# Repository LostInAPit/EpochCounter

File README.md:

# EpochCounter
A counter to count the days since a specific date using an Arduino nano, DS3231 RTC and a 4-digit 7 Segment display

I designed this project to be a simple, self contained display for your workspace, office or anywhere with access to wall power. The main use of the project is to count the days since a specific event, lifestyle change such as sobriety, mental health goals or really any other reason.

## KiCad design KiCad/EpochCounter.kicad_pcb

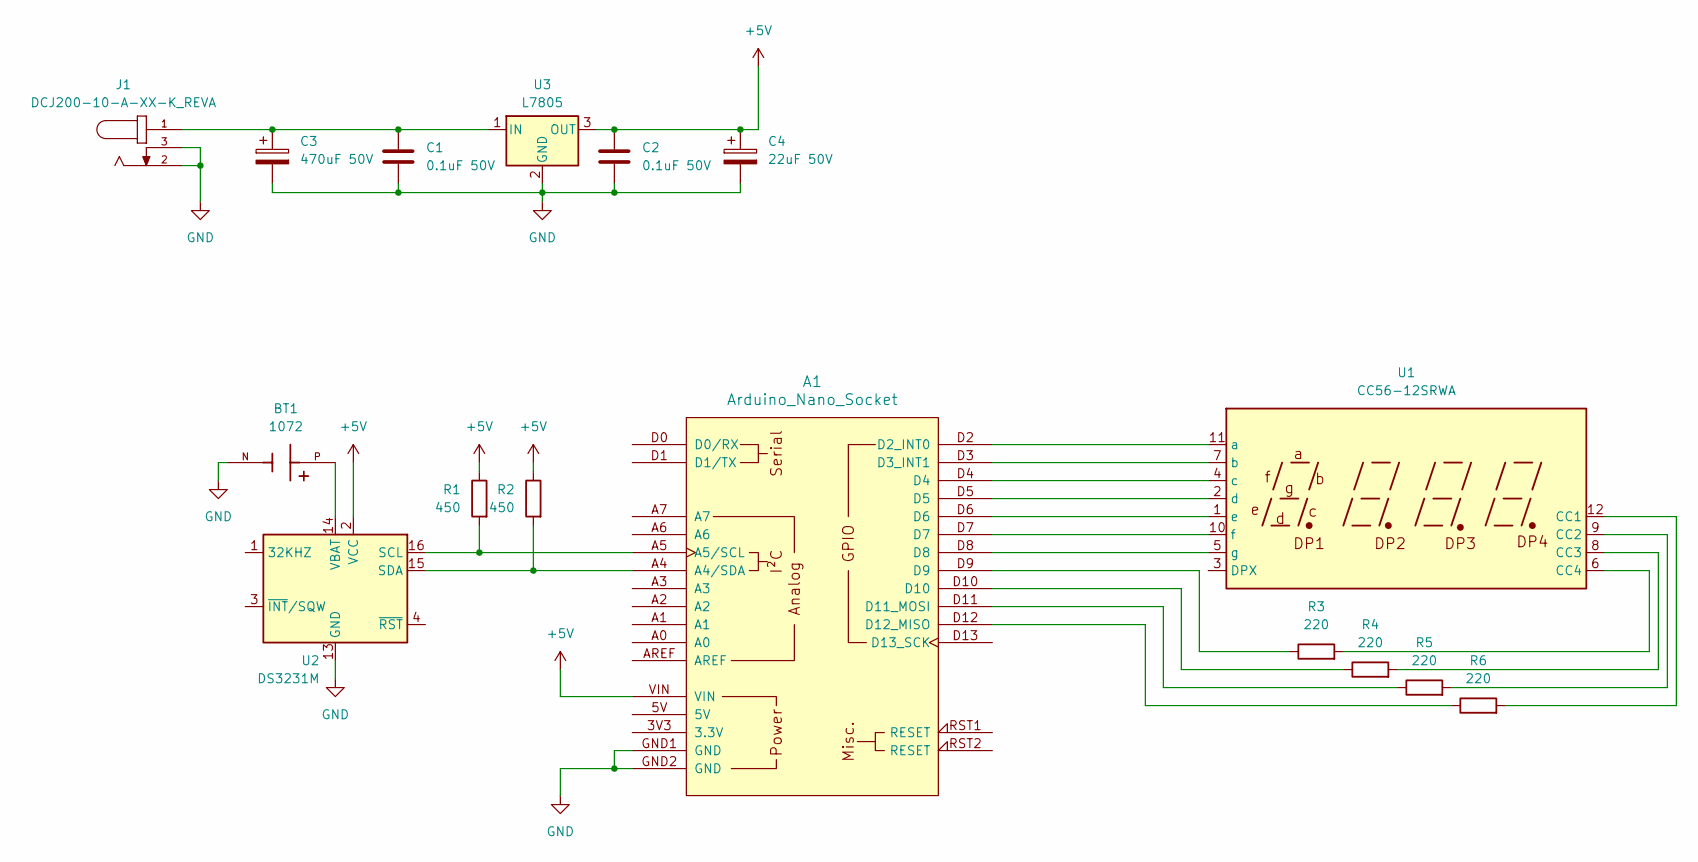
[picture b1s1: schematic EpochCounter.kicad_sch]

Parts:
A1: Arduino_Nano_Socket
BT1: 1072; BAT_1072; PARTREV A
C1, C2: 0.1uF 50V; CP_Radial_D6.3mm_P2.50mm
C3: 470uF 50V; CP_Radial_D10.0mm_P5.00mm
C4: 22uF 50V; CP_Radial_D10.0mm_P5.00mm
J1: DCJ200-10-A-XX-K_REVA; GCT_DCJ200-10-A-XX-K_REVA; PARTREV A
R1, R2: 450; R_1206_3216Metric
R3, R4, R5, R6: 220; R_1206_3216Metric
U1: CC56-12SRWA; CA56-12SRWA
U2: DS3231M; SOIC-16W_7.5x10.3mm_P1.27mm
U3: L7805; TO-220-3_Vertical

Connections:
+5V: A1.VIN, C2.1, C4.1, R1.1, R2.1, U2.2 (VCC), U3.3 (OUT)
GND: A1.GND1 (GND), A1.GND2 (GND), BT1.N, C1.2, C2.2, C3.2, C4.2, J1.2, J1.3, U2.5 (GND), U2.6 (GND), U2.7 (GND), U2.8 (GND), U2.9 (GND), U2.10 (GND), U2.11 (GND), U2.12 (GND), U2.13 (GND), U3.2 (GND)
unnamed: A1.A4 (A4/SDA), R2.2, U2.15 (SDA)
unnamed: A1.A5 (A5/SCL), R1.2, U2.16 (SCL)
unnamed: A1.D2 (D2_INT0), U1.11 (a)
unnamed: A1.D3 (D3_INT1), U1.7 (b)
unnamed: A1.D11 (D11_MOSI), R5.1
unnamed: A1.D12 (D12_MISO), R6.1
unnamed: A1.D9, R3.1
unnamed: A1.D10, R4.1
unnamed: R6.2, U1.12 (CC1)
unnamed: R5.2, U1.9 (CC2)
unnamed: R4.2, U1.8 (CC3)
unnamed: R3.2, U1.6 (CC4)
unnamed: A1.D4, U1.4 (c)
unnamed: A1.D5, U1.2 (d)
unnamed: A1.D6, U1.1 (e)
unnamed: A1.D7, U1.10 (f)
unnamed: A1.D8, U1.5 (g)
unnamed: BT1.P, U2.14 (VBAT)
unnamed: C1.1, C3.1, J1.1, U3.1 (IN)

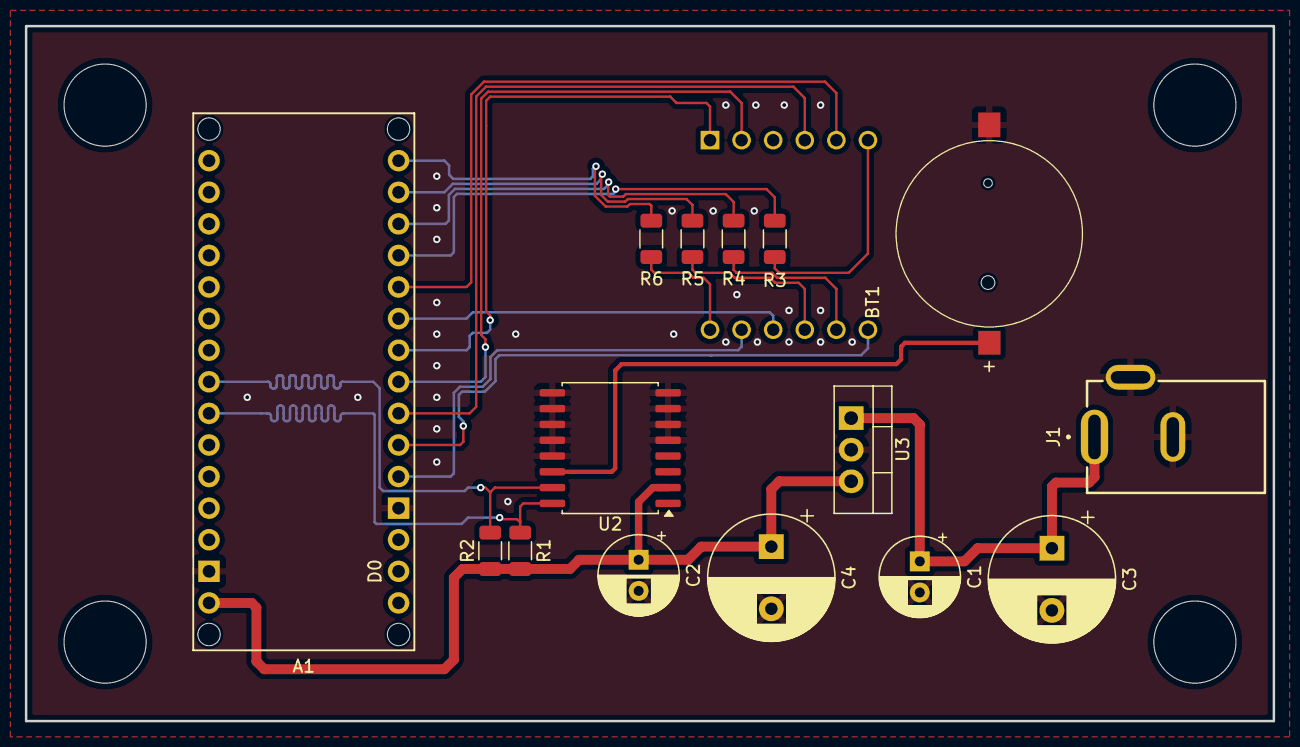
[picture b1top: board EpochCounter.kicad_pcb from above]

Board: 2 copper layers, 100.3 x 55.9 mm, 16 parts (1 on the bottom side), 21 nets.
